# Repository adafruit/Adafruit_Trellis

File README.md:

# CAD & PCB data for the Adafruit Trellis keypad & control PCB

<a href="http://www.adafruit.com/products/1611"><br/>Click here to purchase one from the Adafruit shop</a>

* [Silicone Elastomer 4x4 Button Keypad - for 3mm LEDs](https://www.adafruit.com/product/1611)
* [Small 1.2" 8x8 Ultra Bright White LED Matrix + Backpack](https://www.adafruit.com/product/1614)

So squishy! These silicone elastomer keypads are just waiting for your fingers to press them. Go ahead, squish all you like! (They're durable and easy to clean, just wipe with mild soap and water) These are just like the light up rubber buttons you find on stuff like appliances and tools, but these are open source and easy to integrate into your next project.

Each button is 10mm x 10mm square and 10mm tall. There is 5mm of grid spacing between the buttons. You can 'tile' the button pads edge-to-edge and they'll grid up correctly. You can also cut the pads down if you like, the silicone is very soft. The way they're molded, they give about 3mm of travel when pressed for a very satisfying feel. They are completely quiet, however.

On the bottom of each button is a conductive pad ring which can close a properly design contact underneath. [We have an EagleCad library which has objects for the buttons and optional LEDs so you can use them in your next PCB design.](https://github.com/adafruit/Adafruit_Trellis).

Each button is 10mm tall and can fit a 3mm LED inside quite easily. 5mm LEDs are too big, so stick with 3mm here. The LED is optional, having it or not does not affect the 'action'. but it's nice to backlight buttons. Diffused LEDs are best, [so check out our offerings: the blue, white and red look best, if you're sourcing your own LEDs go for something with 300mcd or greater brightness. Diffused looks better than not.](https://www.adafruit.com/search?q=led+diffused+3mm).

[Chances are you don't want to make your own PCB, so pick up an Adafruit Trellis, our tile-able driver which can control 16 LEDs + these 16 buttons over I2C](https://www.adafruit.com/products/1616).

## License

Adafruit invests time and resources providing this open source design, 
please support Adafruit and open-source hardware by purchasing 
products from Adafruit!

Designed by Adafruit Industries.  
GNU Public License v2
All text above must be included in any redistribution

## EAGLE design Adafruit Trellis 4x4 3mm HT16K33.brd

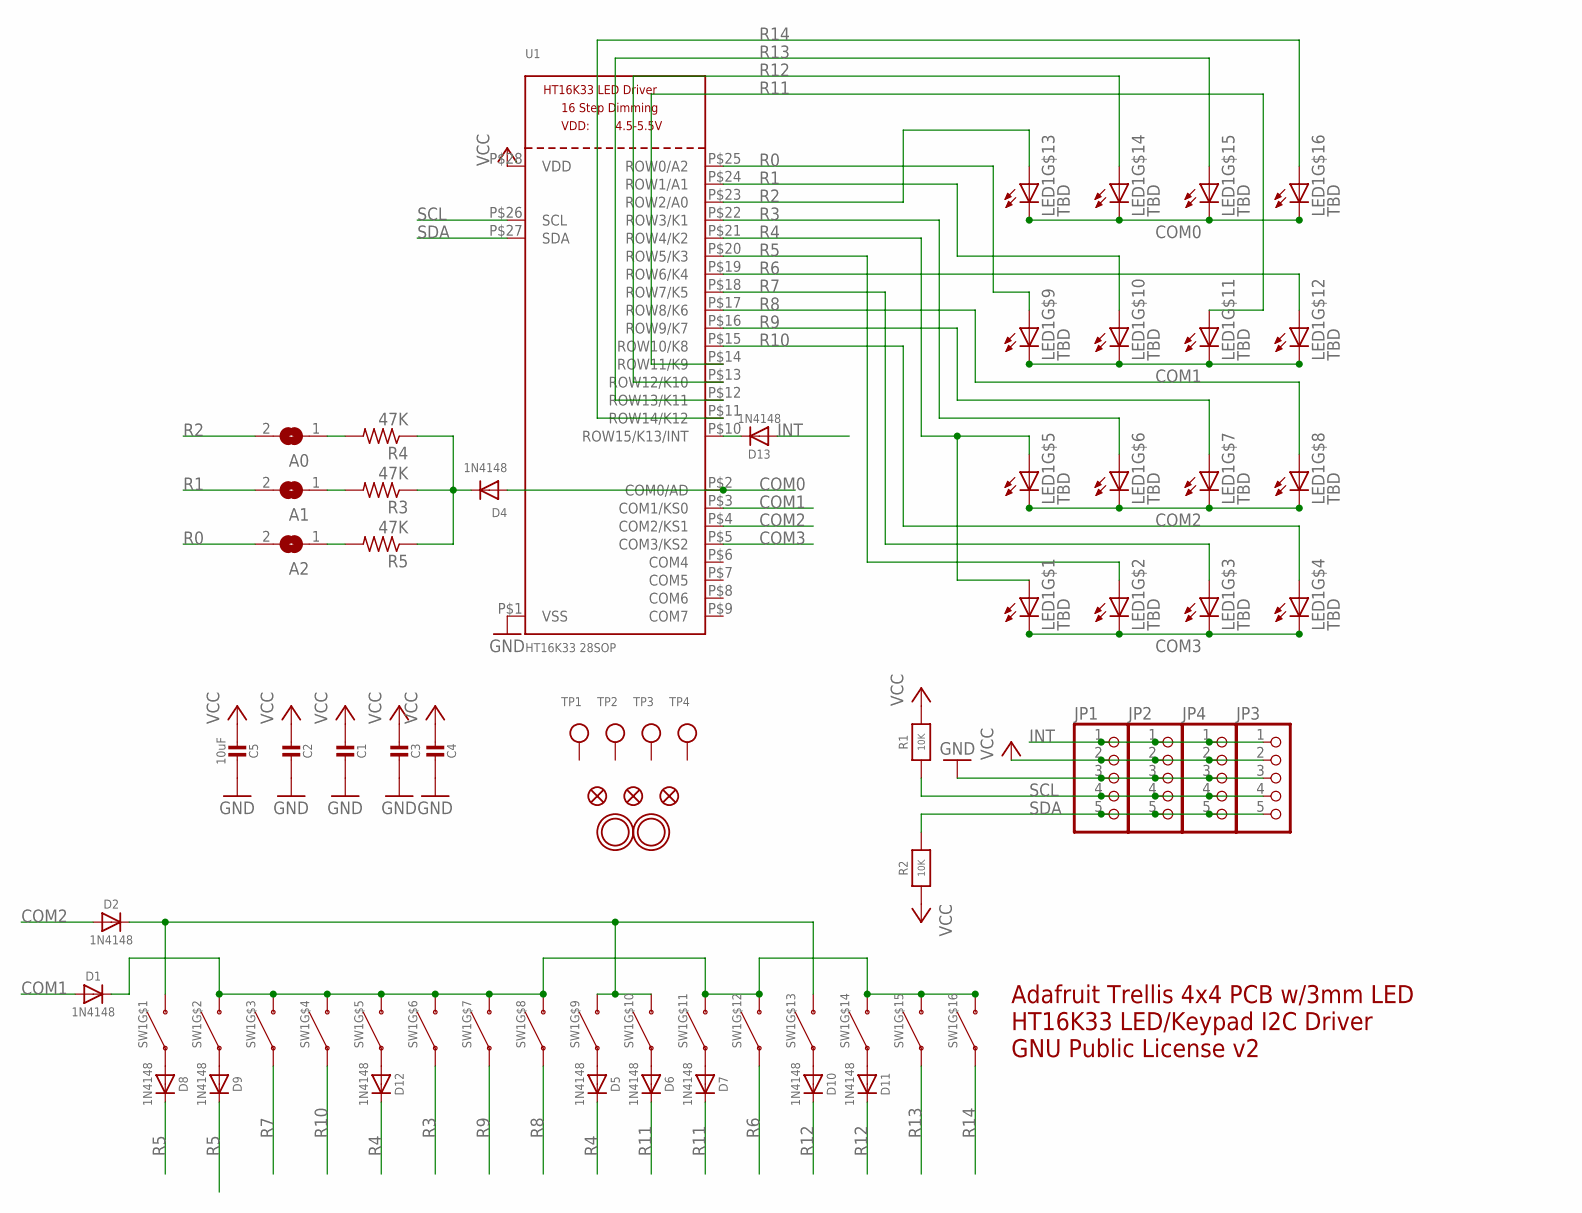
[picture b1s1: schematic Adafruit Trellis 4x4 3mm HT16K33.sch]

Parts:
A0, A1, A2: SOLDERJUMPERREFLOW_NOPASTE; SOLDERJUMPER_REFLOW_NOPASTE
C1, C2, C3, C4: CAP_CERAMIC_0805; _0805
C5: 10uF; _0805
D1, D2, D5, D6, D7, D8, D9, D10, D11, D12, D13: 1N4148; SOD-323
D4: 1N4148; SOD-323F
FID1, FID2, FID3: FIDUCIAL""; FIDUCIAL_1MM
JP1, JP2, JP3, JP4: HEADER-1X5EDGESMT; 1X5_SMT
LED1: TBD; LED3MM-4X4GRID
R1, R2: 10K; _0805
R3, R4, R5: 47K; R0805
SW1: SWITCH-SILICON-4X4GRID-10MM-5.4MM; ELAST_PAD_SQUARE_10MM_5.4MM_4X4GRID
TP1, TP2, TP3, TP4: TESTPOINT; TESTPOINT_SMT
U1: HT16K33 28SOP; SOP28_300MIL
U$1, U$2: MOUNTINGHOLE2.5; MOUNTINGHOLE_2.5_PLATED

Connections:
COM0: D4.A, LED1.K13 (C), LED1.K14 (C), LED1.K15 (C), LED1.K16 (C), U1.P$2 (COM0/AD)
COM1: D1.A, LED1.K9 (C), LED1.K10 (C), LED1.K11 (C), LED1.K12 (C), U1.P$3 (COM1/KS0)
COM2: D2.A, LED1.K5 (C), LED1.K6 (C), LED1.K7 (C), LED1.K8 (C), U1.P$4 (COM2/KS1)
COM3: LED1.K1 (C), LED1.K2 (C), LED1.K3 (C), LED1.K4 (C), U1.P$5 (COM3/KS2)
GND: C1.1, C2.1, C3.1, C4.1, C5.1, JP1.3, JP2.3, JP3.3, JP4.3, U1.P$1 (VSS)
INT: D13.A, JP1.1, JP2.1, JP3.1, JP4.1
unnamed: D2.C, SW1.B1, SW1.B9, SW1.B10, SW1.B13
unnamed: D13.C, U1.P$10 (ROW15/K13/INT)
unnamed: D5.A, SW1.A9
unnamed: D6.A, SW1.A10
unnamed: D1.C, SW1.B2, SW1.B3, SW1.B4, SW1.B5, SW1.B6, SW1.B7, SW1.B8, SW1.B11, SW1.B12, SW1.B14, SW1.B15, SW1.B16
unnamed: D7.A, SW1.A11
unnamed: D8.A, SW1.A1
unnamed: D9.A, SW1.A2
unnamed: A2.1, R5.2
unnamed: D10.A, SW1.A13
unnamed: D11.A, SW1.A14
unnamed: D12.A, SW1.A5
unnamed: D4.C, R3.1, R4.1, R5.1
unnamed: A1.1, R3.2
unnamed: A0.1, R4.2
R0: A2.2, LED1.A9 (A), U1.P$25 (ROW0/A2)
R1: A1.2, LED1.A10 (A), U1.P$24 (ROW1/A1)
R2: A0.2, LED1.A13 (A), U1.P$23 (ROW2/A0)
R3: LED1.A6 (A), SW1.A6, U1.P$22 (ROW3/K1)
R4: D5.C, D12.C, LED1.A1 (A), LED1.A5 (A), U1.P$21 (ROW4/K2)
R5: D8.C, D9.C, LED1.A2 (A), U1.P$20 (ROW5/K3)
R6: LED1.A12 (A), SW1.A12, U1.P$19 (ROW6/K4)
R7: LED1.A3 (A), SW1.A3, U1.P$18 (ROW7/K5)
R8: LED1.A8 (A), SW1.A8, U1.P$17 (ROW8/K6)
R9: LED1.A7 (A), SW1.A7, U1.P$16 (ROW9/K7)
R10: LED1.A4 (A), SW1.A4, U1.P$15 (ROW10/K8)
R11: D6.C, D7.C, LED1.A11 (A), U1.P$14 (ROW11/K9)
R12: D10.C, D11.C, LED1.A14 (A), U1.P$13 (ROW12/K10)
R13: LED1.A15 (A), SW1.A15, U1.P$12 (ROW13/K11)
R14: LED1.A16 (A), SW1.A16, U1.P$11 (ROW14/K12)
SCL: JP1.4, JP2.4, JP3.4, JP4.4, R1.1, U1.P$26 (SCL)
SDA: JP1.5, JP2.5, JP3.5, JP4.5, R2.2, U1.P$27 (SDA)
VCC: C1.2, C2.2, C3.2, C4.2, C5.2, JP1.2, JP2.2, JP3.2, JP4.2, R1.2, R2.1, U1.P$28 (VDD)

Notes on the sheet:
Adafruit Trellis 4x4 PCB w/3mm LED HT16K33 LED/Keypad I2C Driver GNU Public License v2

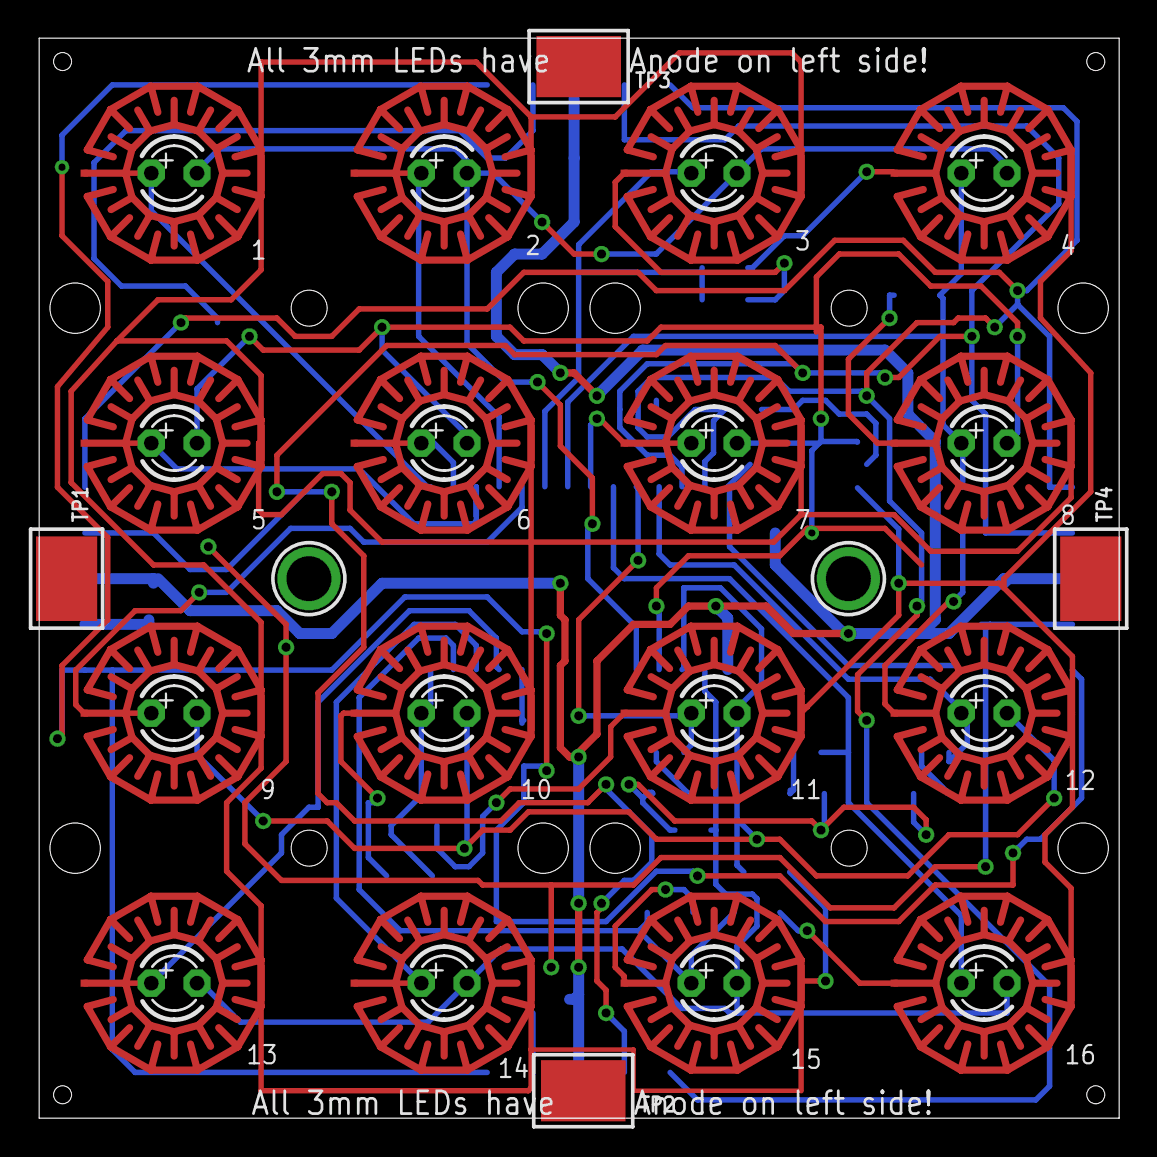
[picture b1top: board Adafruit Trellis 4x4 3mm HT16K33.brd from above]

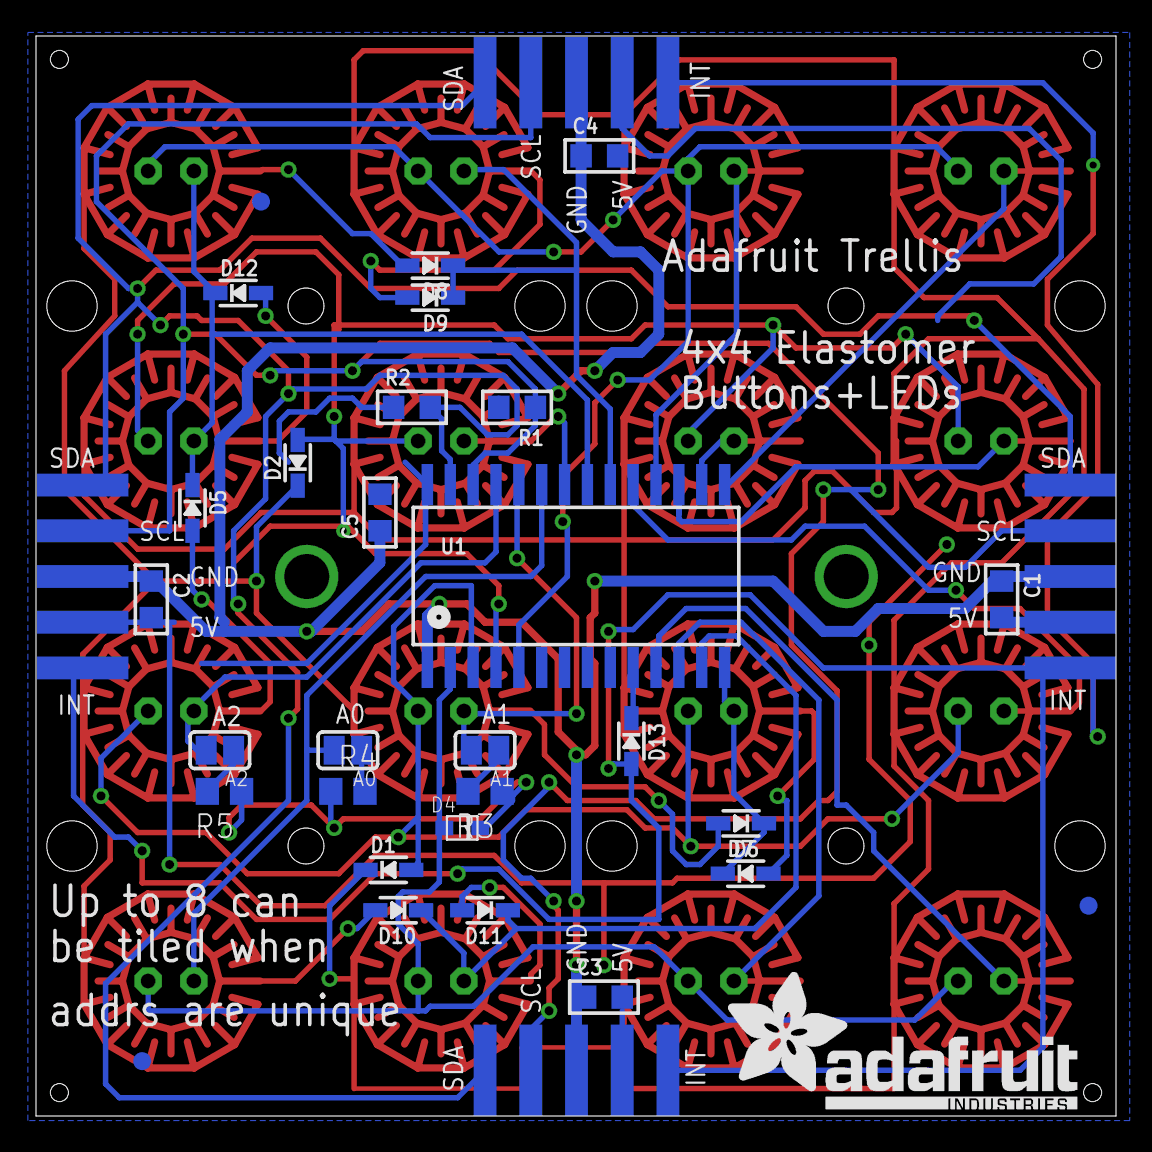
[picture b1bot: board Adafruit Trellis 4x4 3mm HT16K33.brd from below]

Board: 2 copper layers, 60.0 x 60.0 mm, 42 parts (34 on the bottom side), 39 nets.

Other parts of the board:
U$3: ADAFRUIT_TEXT_20MM

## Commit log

2013-12-06 STEP original & STL convert
2013-12-06 Eagle Files
2013-12-06 read me!
2013-12-06 eagle objects
2019-05-08 readme + image

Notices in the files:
parts and their libraries:
microbuilder: This work is placed in the public domain, and may be freely used for commercial and non-commercial work with the following conditions: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
